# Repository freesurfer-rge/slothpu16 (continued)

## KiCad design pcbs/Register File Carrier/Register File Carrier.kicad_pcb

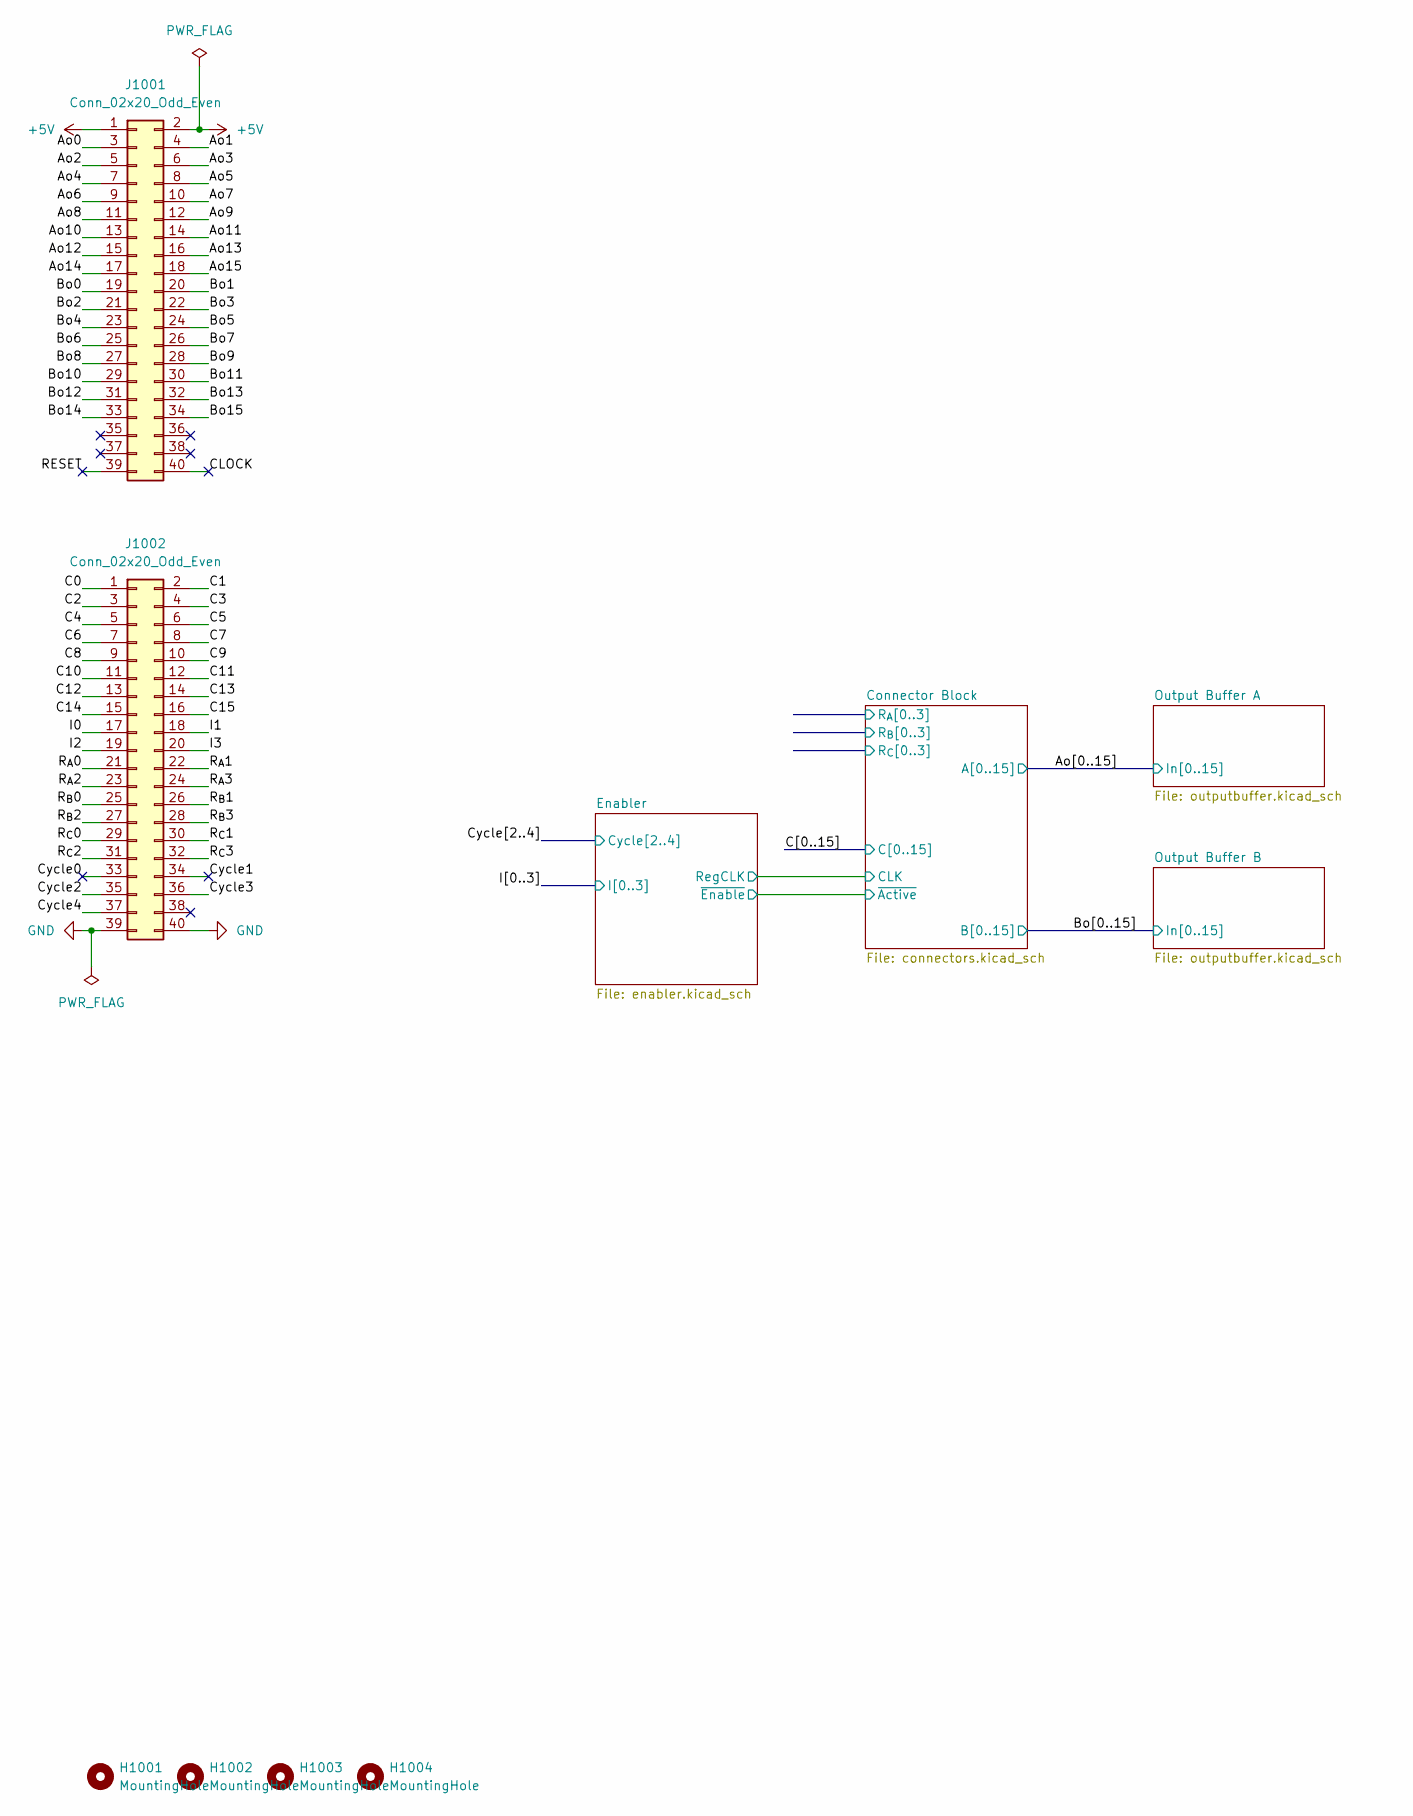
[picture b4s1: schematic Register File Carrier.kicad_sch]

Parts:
H1001, H1002, H1003, H1004: MountingHole; MountingHole_2.7mm_M2.5_ISO7380
J1001, J1002: Conn_02x20_Odd_Even; PinHeader_2x20_P2.54mm_Vertical

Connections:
+5V: J1001.1, J1001.2; also elsewhere on the board
/Ao0: J1001.3; also elsewhere on the board
/Ao1: J1001.4; also elsewhere on the board
/Ao2: J1001.5; also elsewhere on the board
/Ao3: J1001.6; also elsewhere on the board
/Ao4: J1001.7; also elsewhere on the board
/Ao5: J1001.8; also elsewhere on the board
/Ao6: J1001.9; also elsewhere on the board
/Ao7: J1001.10; also elsewhere on the board
/Ao8: J1001.11; also elsewhere on the board
/Ao9: J1001.12; also elsewhere on the board
/Ao10: J1001.13; also elsewhere on the board
/Ao11: J1001.14; also elsewhere on the board
/Ao12: J1001.15; also elsewhere on the board
/Ao13: J1001.16; also elsewhere on the board
/Ao14: J1001.17; also elsewhere on the board
/Ao15: J1001.18; also elsewhere on the board
/Bo0: J1001.19; also elsewhere on the board
/Bo1: J1001.20; also elsewhere on the board
/Bo2: J1001.21; also elsewhere on the board
/Bo3: J1001.22; also elsewhere on the board
/Bo4: J1001.23; also elsewhere on the board
/Bo5: J1001.24; also elsewhere on the board
/Bo6: J1001.25; also elsewhere on the board
/Bo7: J1001.26; also elsewhere on the board
/Bo8: J1001.27; also elsewhere on the board
/Bo9: J1001.28; also elsewhere on the board
/Bo10: J1001.29; also elsewhere on the board
/Bo11: J1001.30; also elsewhere on the board
/Bo12: J1001.31; also elsewhere on the board
/Bo13: J1001.32; also elsewhere on the board
/Bo14: J1001.33; also elsewhere on the board
/Bo15: J1001.34; also elsewhere on the board
/C0: J1002.1; also elsewhere on the board
/C1: J1002.2; also elsewhere on the board
/C2: J1002.3; also elsewhere on the board
/C3: J1002.4; also elsewhere on the board
/C4: J1002.5; also elsewhere on the board
/C5: J1002.6; also elsewhere on the board
/C6: J1002.7; also elsewhere on the board
/C7: J1002.8; also elsewhere on the board
/C8: J1002.9; also elsewhere on the board
/C9: J1002.10; also elsewhere on the board
/C10: J1002.11; also elsewhere on the board
/C11: J1002.12; also elsewhere on the board
/C12: J1002.13; also elsewhere on the board
/C13: J1002.14; also elsewhere on the board
/C14: J1002.15; also elsewhere on the board
/C15: J1002.16; also elsewhere on the board
/CLOCK: J1001.40
/Connector Block/R_{A}0: J1002.21; also elsewhere on the board
/Connector Block/R_{A}1: J1002.22; also elsewhere on the board
/Connector Block/R_{A}2: J1002.23; also elsewhere on the board
/Connector Block/R_{A}3: J1002.24; also elsewhere on the board
/Connector Block/R_{B}0: J1002.25; also elsewhere on the board
/Connector Block/R_{B}1: J1002.26; also elsewhere on the board
/Connector Block/R_{B}2: J1002.27; also elsewhere on the board
/Connector Block/R_{B}3: J1002.28; also elsewhere on the board
/Connector Block/R_{C}0: J1002.29; also elsewhere on the board
/Connector Block/R_{C}1: J1002.30; also elsewhere on the board
/Connector Block/R_{C}2: J1002.31; also elsewhere on the board
/Connector Block/R_{C}3: J1002.32; also elsewhere on the board
/Cycle0: J1002.33
/Cycle1: J1002.34
/Cycle2: J1002.35; also elsewhere on the board
/Cycle3: J1002.36; also elsewhere on the board
/Cycle4: J1002.37; also elsewhere on the board
/I0: J1002.17; also elsewhere on the board
/I1: J1002.18; also elsewhere on the board
/I2: J1002.19; also elsewhere on the board
/I3: J1002.20; also elsewhere on the board
/RESET: J1001.39
GND: J1002.39, J1002.40; also elsewhere on the board

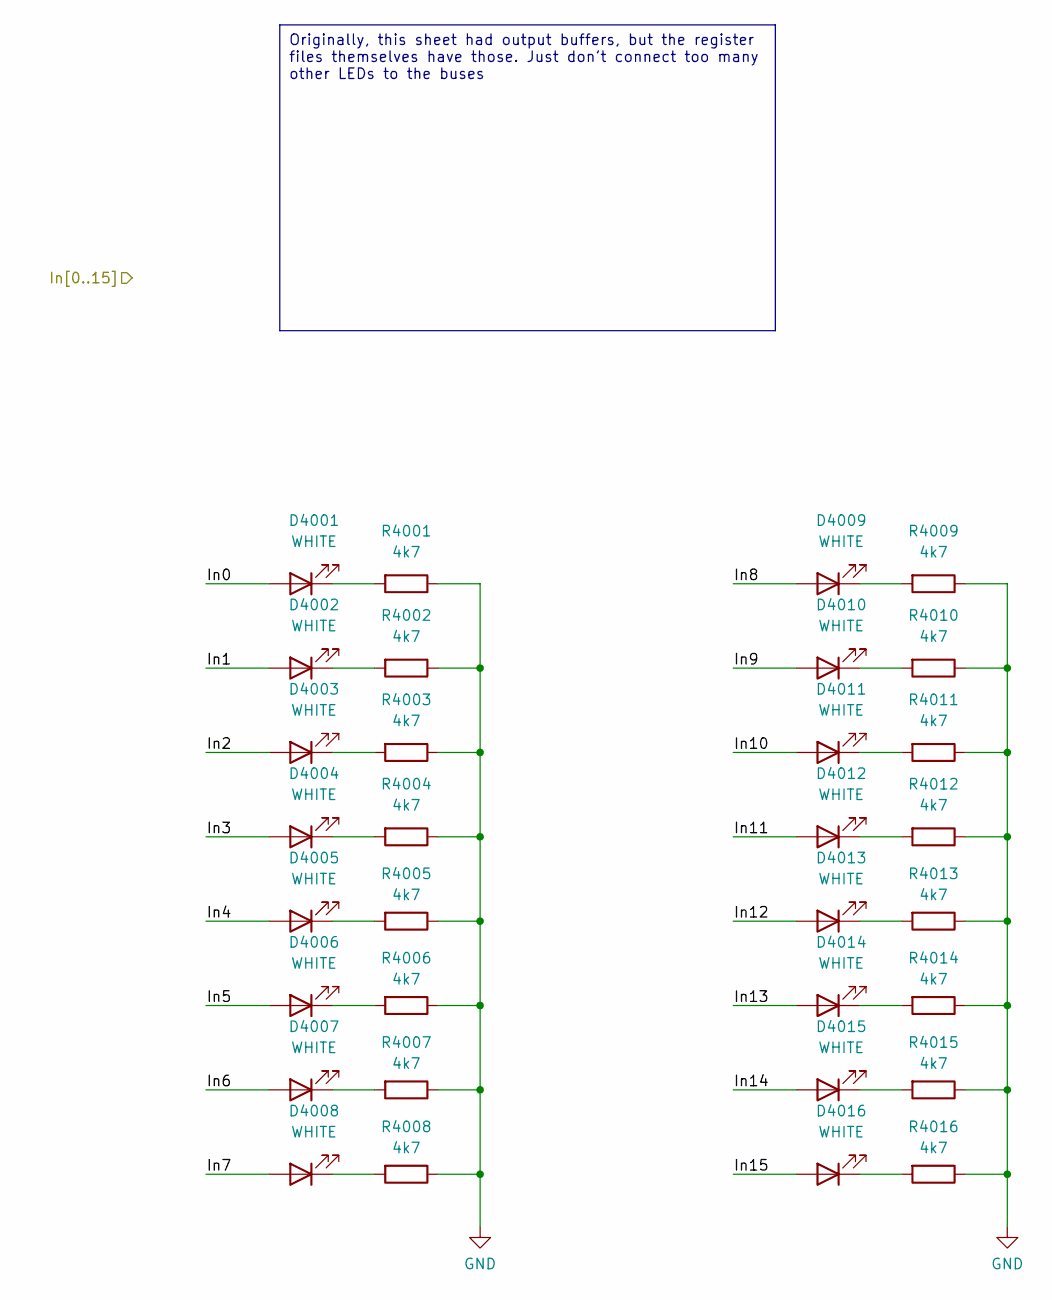
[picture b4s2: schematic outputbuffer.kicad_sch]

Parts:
D4001, D4002, D4003, D4004, D4005, D4006, D4007, D4008, D4009, D4010, D4011, D4012, D4013, D4014, D4015, D4016: WHITE; LED_0603_1608Metric; LCSC C2290
R4001, R4002, R4003, R4004, R4005, R4006, R4007, R4008, R4009, R4010, R4011, R4012, R4013, R4014, R4015, R4016: 4k7; R_0603_1608Metric; LCSC C23162

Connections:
/Ao0: D4001.2 (A); also elsewhere on the board
/Ao1: D4002.2 (A); also elsewhere on the board
/Ao2: D4003.2 (A); also elsewhere on the board
/Ao3: D4004.2 (A); also elsewhere on the board
/Ao4: D4005.2 (A); also elsewhere on the board
/Ao5: D4006.2 (A); also elsewhere on the board
/Ao6: D4007.2 (A); also elsewhere on the board
/Ao7: D4008.2 (A); also elsewhere on the board
/Ao8: D4009.2 (A); also elsewhere on the board
/Ao9: D4010.2 (A); also elsewhere on the board
/Ao10: D4011.2 (A); also elsewhere on the board
/Ao11: D4012.2 (A); also elsewhere on the board
/Ao12: D4013.2 (A); also elsewhere on the board
/Ao13: D4014.2 (A); also elsewhere on the board
/Ao14: D4015.2 (A); also elsewhere on the board
/Ao15: D4016.2 (A); also elsewhere on the board
GND: R4001.1, R4002.1, R4003.1, R4004.1, R4005.1, R4006.1, R4007.1, R4008.1, R4009.1, R4010.1, R4011.1, R4012.1, R4013.1, R4014.1, R4015.1, R4016.1; also elsewhere on the board
unnamed: D4001.1 (K), R4001.2
unnamed: D4002.1 (K), R4002.2
unnamed: D4003.1 (K), R4003.2
unnamed: D4004.1 (K), R4004.2
unnamed: D4005.1 (K), R4005.2
unnamed: D4006.1 (K), R4006.2
unnamed: D4007.1 (K), R4007.2
unnamed: D4008.1 (K), R4008.2
unnamed: D4009.1 (K), R4009.2
unnamed: D4010.1 (K), R4010.2
unnamed: D4011.1 (K), R4011.2
unnamed: D4012.1 (K), R4012.2
unnamed: D4013.1 (K), R4013.2
unnamed: D4014.1 (K), R4014.2
unnamed: D4015.1 (K), R4015.2
unnamed: D4016.1 (K), R4016.2

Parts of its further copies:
D5001, D5002, D5003, D5004, D5005, D5006, D5007, D5008, D5009, D5010, D5011, D5012, D5013, D5014, D5015, D5016: WHITE; LED_0603_1608Metric; LCSC C2290
R5001, R5002, R5003, R5004, R5005, R5006, R5007, R5008, R5009, R5010, R5011, R5012, R5013, R5014, R5015, R5016: 4k7; R_0603_1608Metric; LCSC C23162

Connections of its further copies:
/Bo0: D5001.2 (A); also elsewhere on the board
/Bo1: D5002.2 (A); also elsewhere on the board
/Bo2: D5003.2 (A); also elsewhere on the board
/Bo3: D5004.2 (A); also elsewhere on the board
/Bo4: D5005.2 (A); also elsewhere on the board
/Bo5: D5006.2 (A); also elsewhere on the board
/Bo6: D5007.2 (A); also elsewhere on the board
/Bo7: D5008.2 (A); also elsewhere on the board
/Bo8: D5009.2 (A); also elsewhere on the board
/Bo9: D5010.2 (A); also elsewhere on the board
/Bo10: D5011.2 (A); also elsewhere on the board
/Bo11: D5012.2 (A); also elsewhere on the board
/Bo12: D5013.2 (A); also elsewhere on the board
/Bo13: D5014.2 (A); also elsewhere on the board
/Bo14: D5015.2 (A); also elsewhere on the board
/Bo15: D5016.2 (A); also elsewhere on the board
GND: R5001.1, R5002.1, R5003.1, R5004.1, R5005.1, R5006.1, R5007.1, R5008.1, R5009.1, R5010.1, R5011.1, R5012.1, R5013.1, R5014.1, R5015.1, R5016.1; also elsewhere on the board
unnamed: D5001.1 (K), R5001.2
unnamed: D5002.1 (K), R5002.2
unnamed: D5003.1 (K), R5003.2
unnamed: D5004.1 (K), R5004.2
unnamed: D5005.1 (K), R5005.2
unnamed: D5006.1 (K), R5006.2
unnamed: D5007.1 (K), R5007.2
unnamed: D5008.1 (K), R5008.2
unnamed: D5009.1 (K), R5009.2
unnamed: D5010.1 (K), R5010.2
unnamed: D5011.1 (K), R5011.2
unnamed: D5012.1 (K), R5012.2
unnamed: D5013.1 (K), R5013.2
unnamed: D5014.1 (K), R5014.2
unnamed: D5015.1 (K), R5015.2
unnamed: D5016.1 (K), R5016.2

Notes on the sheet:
Originally, this sheet had output buffers, but the register files themselves have those. Just don't connect too many other LEDs to the buses

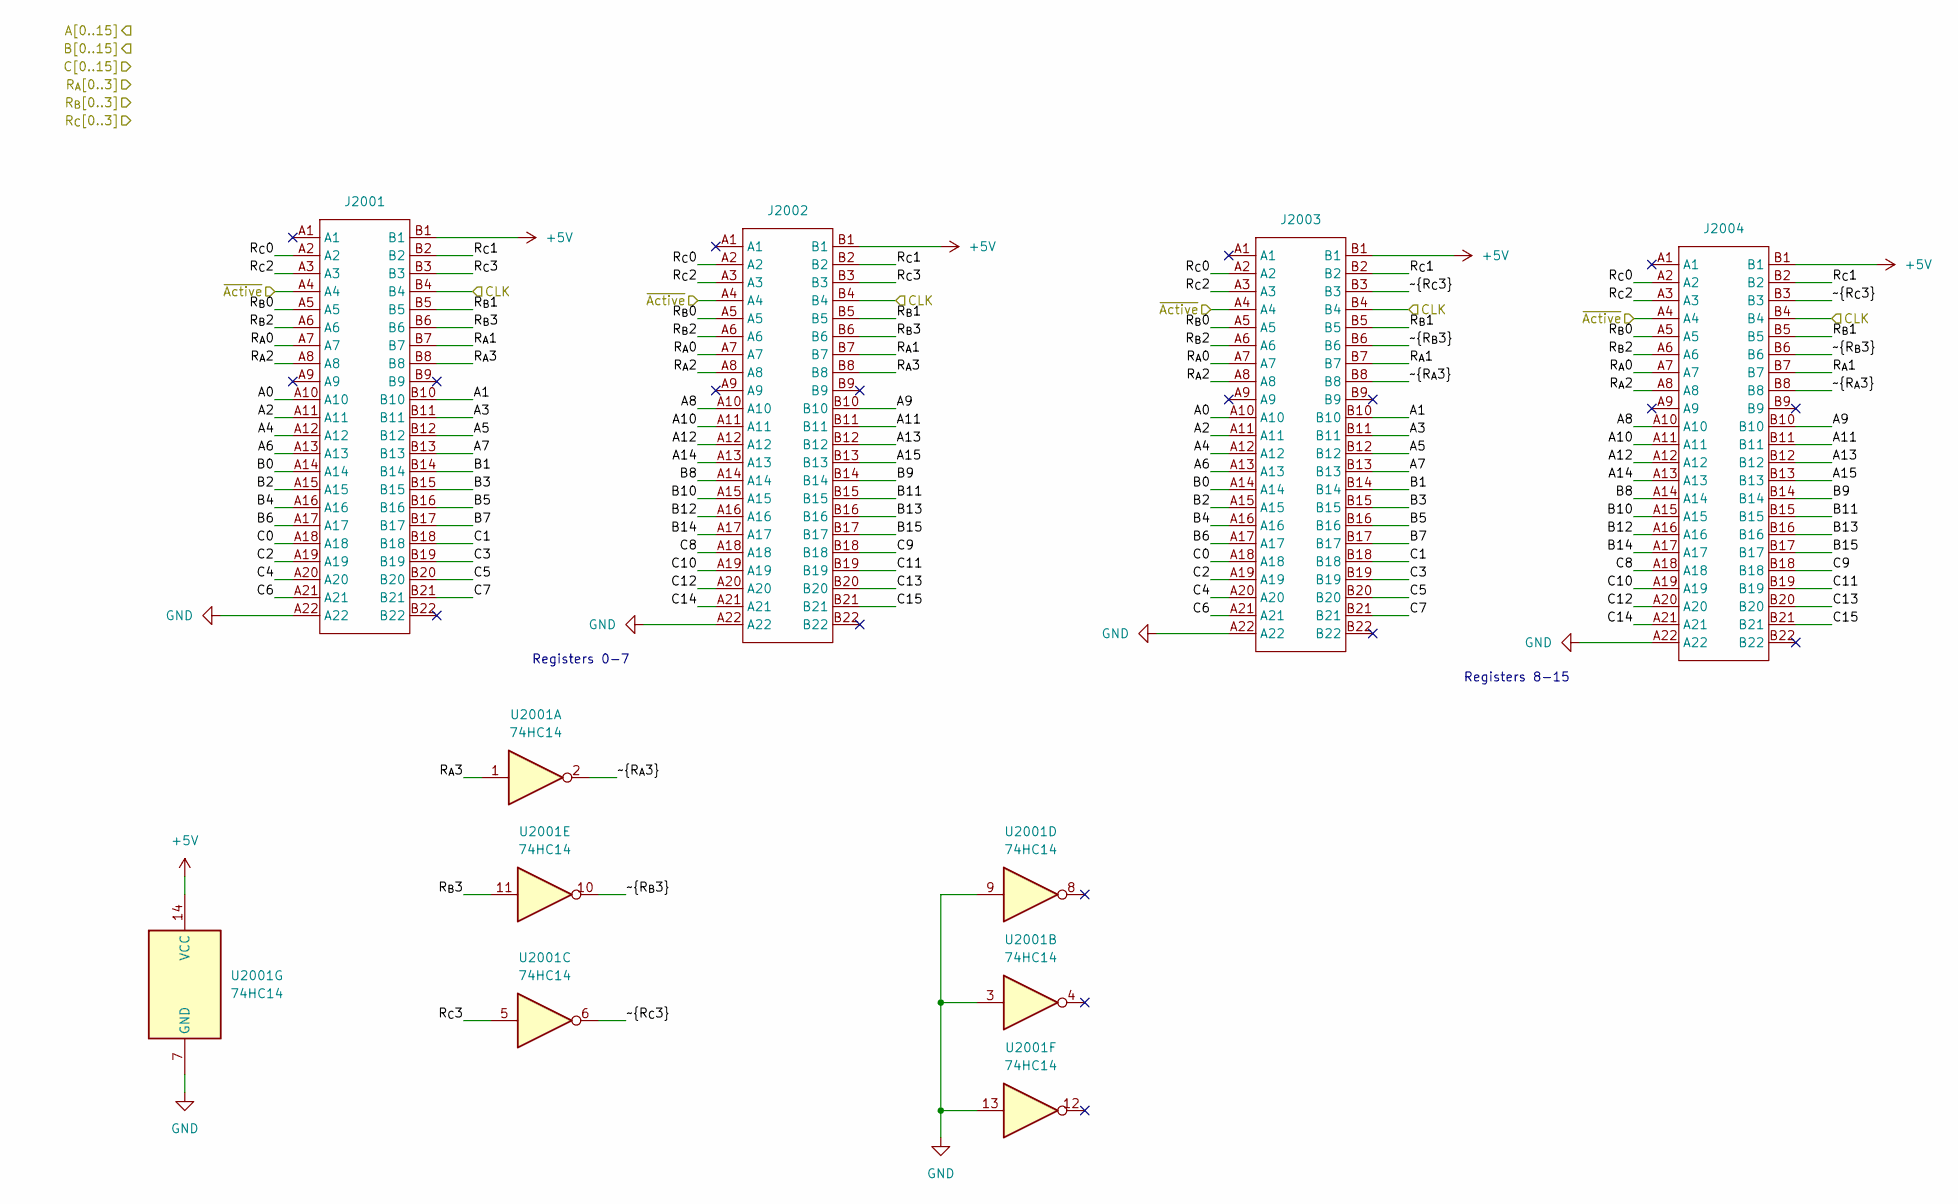
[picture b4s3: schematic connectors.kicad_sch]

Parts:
J2001, J2002, J2003, J2004: TE-5530843-4-Mount
U2001: 74HC14; SOIC-14_3.9x8.7mm_P1.27mm; LCSC C5605

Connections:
+5V: J2001.B1, J2002.B1, J2003.B1, J2004.B1, U2001.14 (VCC); also elsewhere on the board
/Ao0: J2001.A10, J2003.A10; also elsewhere on the board
/Ao1: J2001.B10, J2003.B10; also elsewhere on the board
/Ao2: J2001.A11, J2003.A11; also elsewhere on the board
/Ao3: J2001.B11, J2003.B11; also elsewhere on the board
/Ao4: J2001.A12, J2003.A12; also elsewhere on the board
/Ao5: J2001.B12, J2003.B12; also elsewhere on the board
/Ao6: J2001.A13, J2003.A13; also elsewhere on the board
/Ao7: J2001.B13, J2003.B13; also elsewhere on the board
/Ao8: J2002.A10, J2004.A10; also elsewhere on the board
/Ao9: J2002.B10, J2004.B10; also elsewhere on the board
/Ao10: J2002.A11, J2004.A11; also elsewhere on the board
/Ao11: J2002.B11, J2004.B11; also elsewhere on the board
/Ao12: J2002.A12, J2004.A12; also elsewhere on the board
/Ao13: J2002.B12, J2004.B12; also elsewhere on the board
/Ao14: J2002.A13, J2004.A13; also elsewhere on the board
/Ao15: J2002.B13, J2004.B13; also elsewhere on the board
/Bo0: J2001.A14, J2003.A14; also elsewhere on the board
/Bo1: J2001.B14, J2003.B14; also elsewhere on the board
/Bo2: J2001.A15, J2003.A15; also elsewhere on the board
/Bo3: J2001.B15, J2003.B15; also elsewhere on the board
/Bo4: J2001.A16, J2003.A16; also elsewhere on the board
/Bo5: J2001.B16, J2003.B16; also elsewhere on the board
/Bo6: J2001.A17, J2003.A17; also elsewhere on the board
/Bo7: J2001.B17, J2003.B17; also elsewhere on the board
/Bo8: J2002.A14, J2004.A14; also elsewhere on the board
/Bo9: J2002.B14, J2004.B14; also elsewhere on the board
/Bo10: J2002.A15, J2004.A15; also elsewhere on the board
/Bo11: J2002.B15, J2004.B15; also elsewhere on the board
/Bo12: J2002.A16, J2004.A16; also elsewhere on the board
/Bo13: J2002.B16, J2004.B16; also elsewhere on the board
/Bo14: J2002.A17, J2004.A17; also elsewhere on the board
/Bo15: J2002.B17, J2004.B17; also elsewhere on the board
/C0: J2001.A18, J2003.A18; also elsewhere on the board
/C1: J2001.B18, J2003.B18; also elsewhere on the board
/C2: J2001.A19, J2003.A19; also elsewhere on the board
/C3: J2001.B19, J2003.B19; also elsewhere on the board
/C4: J2001.A20, J2003.A20; also elsewhere on the board
/C5: J2001.B20, J2003.B20; also elsewhere on the board
/C6: J2001.A21, J2003.A21; also elsewhere on the board
/C7: J2001.B21, J2003.B21; also elsewhere on the board
/C8: J2002.A18, J2004.A18; also elsewhere on the board
/C9: J2002.B18, J2004.B18; also elsewhere on the board
/C10: J2002.A19, J2004.A19; also elsewhere on the board
/C11: J2002.B19, J2004.B19; also elsewhere on the board
/C12: J2002.A20, J2004.A20; also elsewhere on the board
/C13: J2002.B20, J2004.B20; also elsewhere on the board
/C14: J2002.A21, J2004.A21; also elsewhere on the board
/C15: J2002.B21, J2004.B21; also elsewhere on the board
/Connector Block/CLK: J2001.B4, J2002.B4, J2003.B4, J2004.B4; also elsewhere on the board
/Connector Block/R_{A}0: J2001.A7, J2002.A7, J2003.A7, J2004.A7; also elsewhere on the board
/Connector Block/R_{A}1: J2001.B7, J2002.B7, J2003.B7, J2004.B7; also elsewhere on the board
/Connector Block/R_{A}2: J2001.A8, J2002.A8, J2003.A8, J2004.A8; also elsewhere on the board
/Connector Block/R_{A}3: J2001.B8, J2002.B8, U2001.1; also elsewhere on the board
/Connector Block/R_{B}0: J2001.A5, J2002.A5, J2003.A5, J2004.A5; also elsewhere on the board
/Connector Block/R_{B}1: J2001.B5, J2002.B5, J2003.B5, J2004.B5; also elsewhere on the board
/Connector Block/R_{B}2: J2001.A6, J2002.A6, J2003.A6, J2004.A6; also elsewhere on the board
/Connector Block/R_{B}3: J2001.B6, J2002.B6, U2001.11; also elsewhere on the board
/Connector Block/R_{C}0: J2001.A2, J2002.A2, J2003.A2, J2004.A2; also elsewhere on the board
/Connector Block/R_{C}1: J2001.B2, J2002.B2, J2003.B2, J2004.B2; also elsewhere on the board
/Connector Block/R_{C}2: J2001.A3, J2002.A3, J2003.A3, J2004.A3; also elsewhere on the board
/Connector Block/R_{C}3: J2001.B3, J2002.B3, U2001.5; also elsewhere on the board
/Connector Block/~Active: J2001.A4, J2002.A4, J2003.A4, J2004.A4; also elsewhere on the board
/Connector Block/~R_{A3}: J2003.B8, J2004.B8, U2001.2
/Connector Block/~R_{B3}: J2003.B6, J2004.B6, U2001.10
/Connector Block/~R_{C3}: J2003.B3, J2004.B3, U2001.6
GND: J2001.A22, J2002.A22, J2003.A22, J2004.A22, U2001.3, U2001.7 (GND), U2001.9, U2001.13; also elsewhere on the board

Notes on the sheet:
Registers 8-15
Registers 0-7

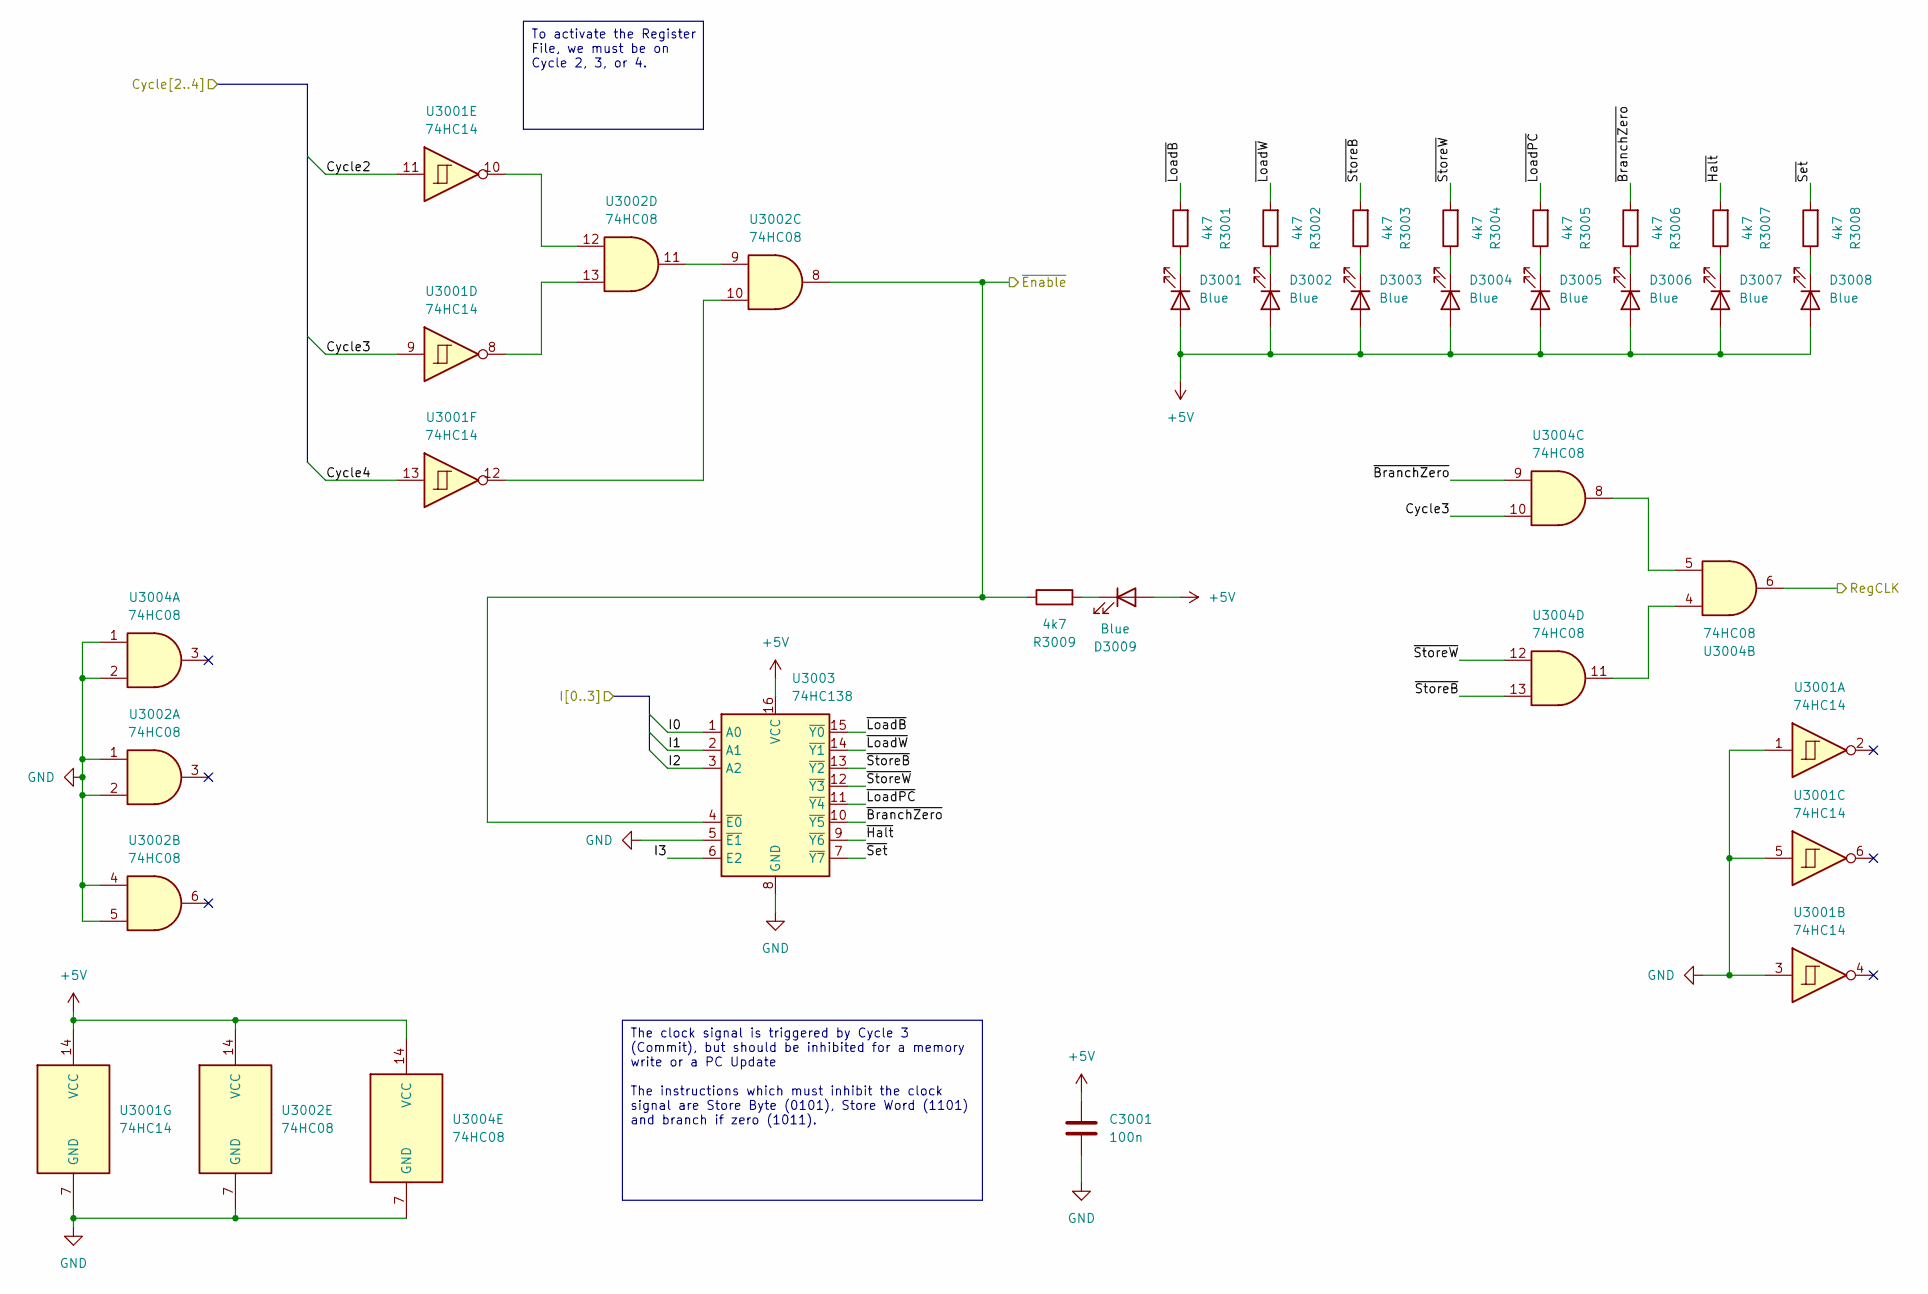
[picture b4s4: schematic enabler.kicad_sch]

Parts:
C3001: 100n; C_0603_1608Metric; LCSC C14663
D3001, D3002, D3003, D3004, D3005, D3006, D3007, D3008, D3009: Blue; LED_0603_1608Metric; LCSC C72041
R3001, R3002, R3003, R3004, R3005, R3006, R3007, R3008, R3009: 4k7; R_0603_1608Metric; LCSC C23162
U3001: 74HC14; SOIC-14_3.9x8.7mm_P1.27mm; LCSC C5605
U3002, U3004: 74HC08; SOIC-14_3.9x8.7mm_P1.27mm; LCSC C5593
U3003: 74HC138; DIP-16_W7.62mm_Socket

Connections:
+5V: C3001.1, D3001.2 (A), D3002.2 (A), D3003.2 (A), D3004.2 (A), D3005.2 (A), D3006.2 (A), D3007.2 (A), D3008.2 (A), D3009.2 (A), U3001.14 (VCC), U3002.14 (VCC), U3003.16 (VCC), U3004.14 (VCC); also elsewhere on the board
/Connector Block/CLK: U3004.6; also elsewhere on the board
/Connector Block/~Active: R3009.1, U3002.8, U3003.4 (~E0); also elsewhere on the board
/Cycle2: U3001.11; also elsewhere on the board
/Cycle3: U3001.9, U3004.10; also elsewhere on the board
/Cycle4: U3001.13; also elsewhere on the board
/Enabler/~BranchZero: R3006.2, U3003.10 (~Y5), U3004.9
/Enabler/~Halt: R3007.2, U3003.9 (~Y6)
/Enabler/~LoadB: R3001.2, U3003.15 (~Y0)
/Enabler/~LoadPC: R3005.2, U3003.11 (~Y4)
/Enabler/~LoadW: R3002.2, U3003.14 (~Y1)
/Enabler/~Set: R3008.2, U3003.7 (~Y7)
/Enabler/~StoreB: R3003.2, U3003.13 (~Y2), U3004.13
/Enabler/~StoreW: R3004.2, U3003.12 (~Y3), U3004.12
/I0: U3003.1 (A0); also elsewhere on the board
/I1: U3003.2 (A1); also elsewhere on the board
/I2: U3003.3 (A2); also elsewhere on the board
/I3: U3003.6 (E2); also elsewhere on the board
GND: C3001.2, U3001.1, U3001.3, U3001.5, U3001.7 (GND), U3002.1, U3002.2, U3002.4, U3002.5, U3002.7 (GND), U3003.5 (~E1), U3003.8 (GND), U3004.1, U3004.2, U3004.7 (GND); also elsewhere on the board
unnamed: D3001.1 (K), R3001.1
unnamed: D3002.1 (K), R3002.1
unnamed: D3003.1 (K), R3003.1
unnamed: D3004.1 (K), R3004.1
unnamed: D3005.1 (K), R3005.1
unnamed: D3006.1 (K), R3006.1
unnamed: D3007.1 (K), R3007.1
unnamed: D3008.1 (K), R3008.1
unnamed: D3009.1 (K), R3009.2
unnamed: U3001.8, U3002.13
unnamed: U3001.10, U3002.12
unnamed: U3001.12, U3002.10
unnamed: U3002.9, U3002.11
unnamed: U3004.5, U3004.8
unnamed: U3004.4, U3004.11

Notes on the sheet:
The clock signal is triggered by Cycle 3 (Commit), but should be inhibited for a memory write or a PC Update The instructions which must inhibit the clock signal are Store Byte (0101), Store Word (1101) and branch if zero (1011).
To activate the Register File, we must be on Cycle 2, 3, or 4.

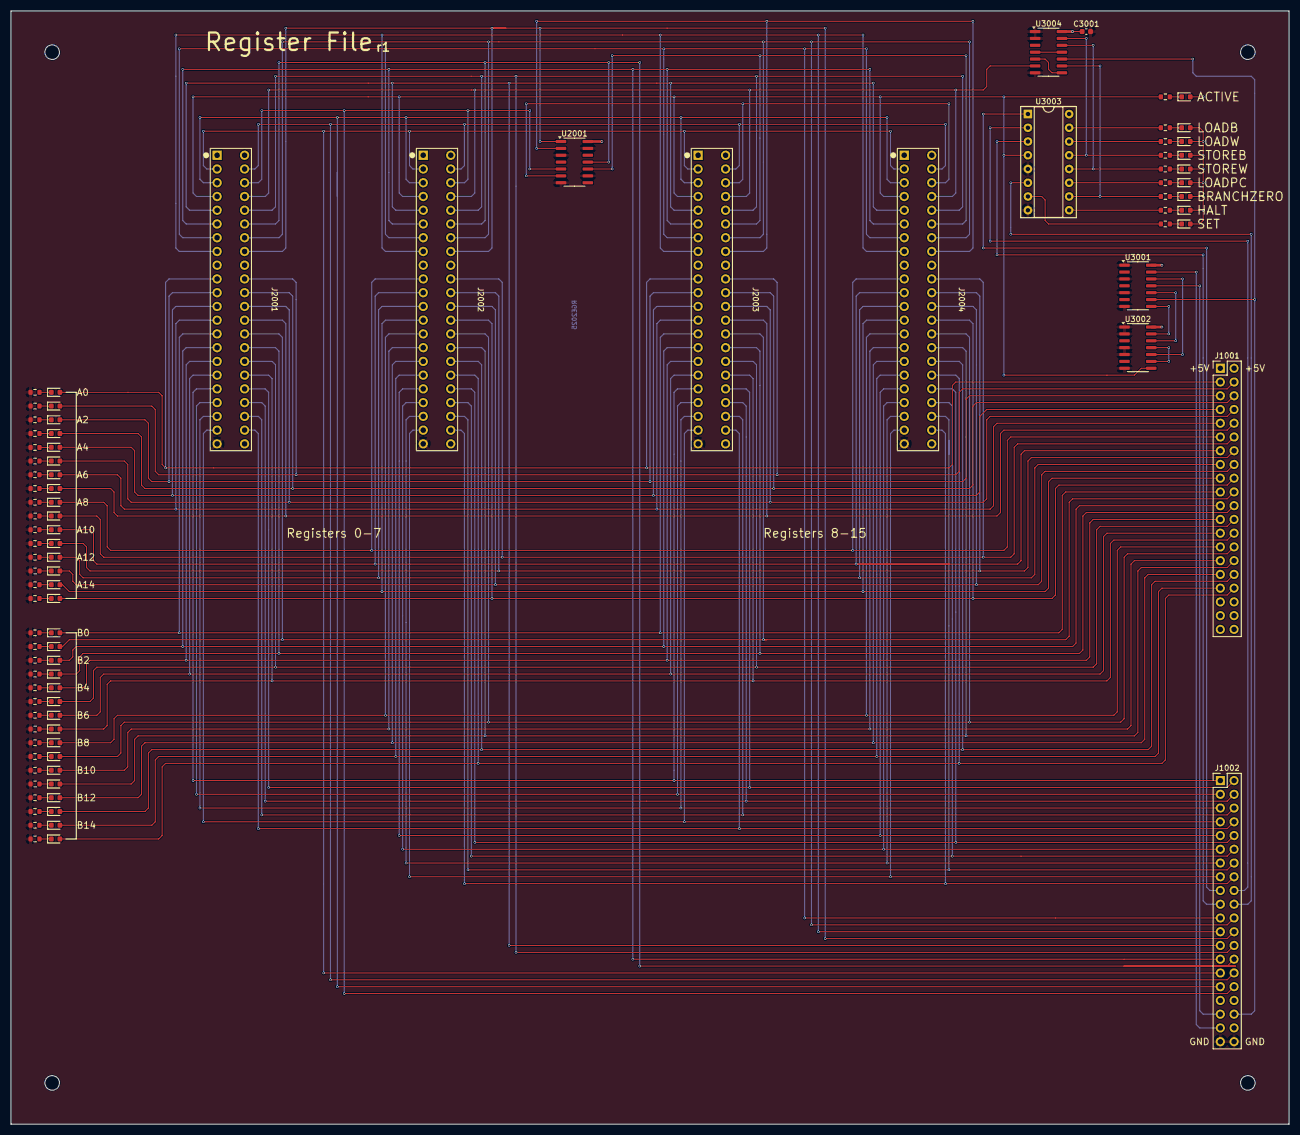
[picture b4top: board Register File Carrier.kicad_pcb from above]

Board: 2 copper layers, 236.2 x 205.7 mm, 98 parts (0 on the bottom side), 129 nets.
